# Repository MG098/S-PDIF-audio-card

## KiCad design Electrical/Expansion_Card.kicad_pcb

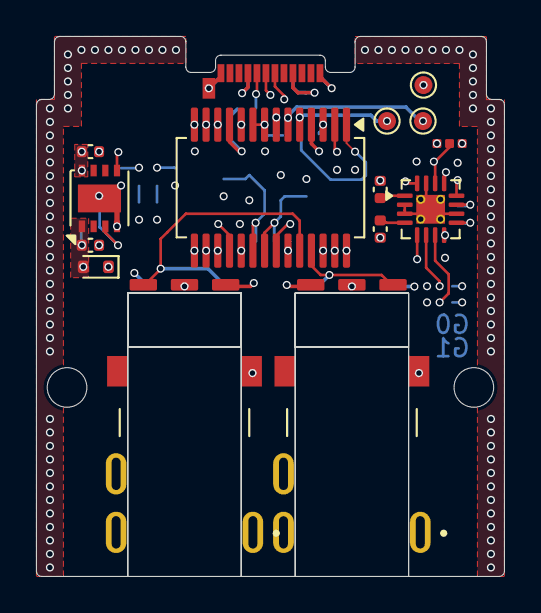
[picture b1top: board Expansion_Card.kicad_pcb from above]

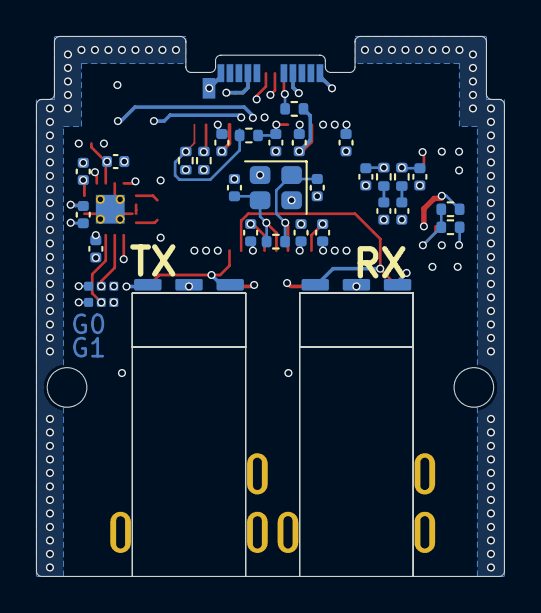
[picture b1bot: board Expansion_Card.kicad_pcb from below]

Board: 6 copper layers, 26.0 x 30.0 mm, 50 parts (31 on the bottom side), 42 nets.

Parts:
C1, C2, C5, C6: 10uF; C_0402_1005Metric
C3, C4: 8pF; C_0402_1005Metric
C7, C8, C9, C10, C11, C12, C13, C14, C15, C18, C19: 1uF; C_0402_1005Metric
C16, C17: 2.2uF; C_0402_1005Metric
C20, C21: 1nF; C_0402_1005Metric
D1: CDBU0130-HF; D_SOD-523
H1, H2: MountingHole; MountingHole_2.2mm_M2
J1, J2: SJ-3501-SMT-TR; CUI_SJ-3501-SMT-TR
JP1, JP2, JP3: SolderJumper_3_Open; Jumper_small_straight
P1: USB_C_Plug_USB2.0; USB_C_Plug_Molex_105444
P2, P3, P4, P5: TX_RX_module
R1: 5.1k; R_0402_1005Metric
R2: 1.5k; R_0402_1005Metric
R3, R4: 22; R_0402_1005Metric
R5: 1M; R_0402_1005Metric
R6: 150k; R_0402_1005Metric
R7, R8: 1k; R_0402_1005Metric
R9: 300k; R_0402_1005Metric
TP5, TP6, TP7: TestPoint; TestPoint_Pad_D1.0mm
U2: PCM2906; SSOP-28_5.3x10.2mm_P0.65mm
U3: TPA6132A2RTE; WQFN-16-1EP_3x3mm_P0.5mm_EP1.6x1.6mm_ThermalVias
U4: LDLN050PUR; DFN-8-1EP_3x3mm_P0.65mm_EP1.55x2.4mm
Y1: 120-8-36B-CWY-TR; Crystal_SMD_2520-4Pin_2.5x2.0mm

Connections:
/EN: U2.28 (~SSPND), U3.13 (EN), U4.5 (EN)
/G0: JP1.2 (C), U3.6 (G0)
/G1: JP2.2 (C), U3.7 (G1)
/USB_DN: P1.A7 (D-), R4.1
/USB_DP: P1.A6 (D+), R3.1
GND: C1.2, C2.2, C3.2, C4.2, C5.2, C6.2, C7.2, C8.2, C9.2, C10.1, C11.1, C14.1, C16.1, C17.2, C20.2, C21.1, J1.1, J1.5, J2.1, J2.5, JP1.1 (A), JP2.1 (A), P1.A1 (GND), P1.A12 (GND), P1.B1 (GND), P1.B12 (GND), P1.S1 (SHIELD), P2.2 (GND), P3.1 (GND), P4.1 (GND), P5.2 (GND), R1.2, R6.1, U2.4 (DGNDU), U2.11 (AGNDC), U2.18 (AGNDP), U2.22 (AGNDX), U2.26 (DGND), U3.2 (INL+), U3.3 (INR+), U3.10 (PGND), U3.15 (SGND), U3.17 (EP), U4.4 (GND), U4.9 (GND), Y1.2 (G), Y1.4 (G)
unnamed: C18.1, J2.4
unnamed: C18.2, R8.1
unnamed: C19.1, J2.3
unnamed: C19.2, R7.1
unnamed: C17.1, JP3.2 (C), U3.14 (VDD)
unnamed: P1.A5 (CC), R1.1
unnamed: P2.1 (OUT), P5.1 (OUT), U2.24 (DIN)
unnamed: P3.3 (IN), P4.3 (IN), U2.25 (DOUT)
unnamed: R2.2, R3.2, U2.1 (D+)
unnamed: R4.2, U2.2 (D-)
unnamed: TP5.1, U2.5 (HID0)
unnamed: TP6.1, U2.6 (HID1)
unnamed: TP7.1, U2.7 (HID2)
unnamed: C7.1, U2.17 (VCCP1I)
unnamed: C8.1, U2.19 (VCCP2I)
unnamed: C9.1, U2.23 (VCCXI)
unnamed: C6.1, U2.14 (VCOM)
unnamed: C21.2, R8.2, U2.12 (VINL)
unnamed: C20.1, R7.2, U2.13 (VINR)
unnamed: C13.1, U2.16 (VOUTL)
unnamed: C12.1, U2.15 (VOUTR)
unnamed: C4.1, R5.1, U2.21 (XTI), Y1.3
unnamed: C3.1, R5.2, U2.20 (XTO), Y1.1
unnamed: C15.1, U3.9 (CPN)
unnamed: C15.2, U3.11 (CPP)
unnamed: C16.2, U3.12 (HPVDD)
unnamed: C14.2, U3.8 (HPVSS)
unnamed: C13.2, U3.1 (INL-)
unnamed: C12.2, U3.4 (INR-)
unnamed: J1.4, U3.16 (OUTL)
unnamed: J1.3, U3.5 (OUTR)
unnamed: R6.2, R9.1, U4.3 (FB)
VBUS: C1.1, C11.2, JP3.3 (B), P1.A4 (VBUS), P1.A9 (VBUS), P1.B4 (VBUS), P1.B9 (VBUS), U2.3 (VBUS), U4.8 (VIN)
VCC: C2.1, D1.2 (A), JP1.3 (B), JP2.3 (B), JP3.1 (A), P2.3 (VCC), P3.2 (VCC), P4.2 (VCC), P5.3 (VCC), R9.2, U4.1 (VOUT)
VCCI: C5.1, D1.1 (K), U2.10 (VCCCI)
VDDI: C10.2, R2.1, U2.8 (SEL0), U2.9 (SEL1), U2.27 (VDDI)

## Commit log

2026-02-15 Added parts
2026-02-24 New footprints and components added
2026-02-25 Schematic completed + basic layout
2026-02-26 Routing + output

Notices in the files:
Electrical/Expansion_Card.kicad_pcb:
This work is licensed under a Creative Commons Attribution 4.0 International License
